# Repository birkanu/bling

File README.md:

# Bling

Bling is a smart ring that lets you control any bluetooth enabled device using hand gestures.

This repository contains:
* [bling-js](https://github.com/birkanu/bling/tree/master/bling-js) (Bling JavaScript Bindings)
* [bling-connection-js](https://github.com/birkanu/bling/tree/master/bling-connection-js) (Bling Connection: JavaScript Component)
* [bling-connection-arduino](https://github.com/birkanu/bling/tree/master/bling-connection-arduino) (Bling Connection: Arduino Component)

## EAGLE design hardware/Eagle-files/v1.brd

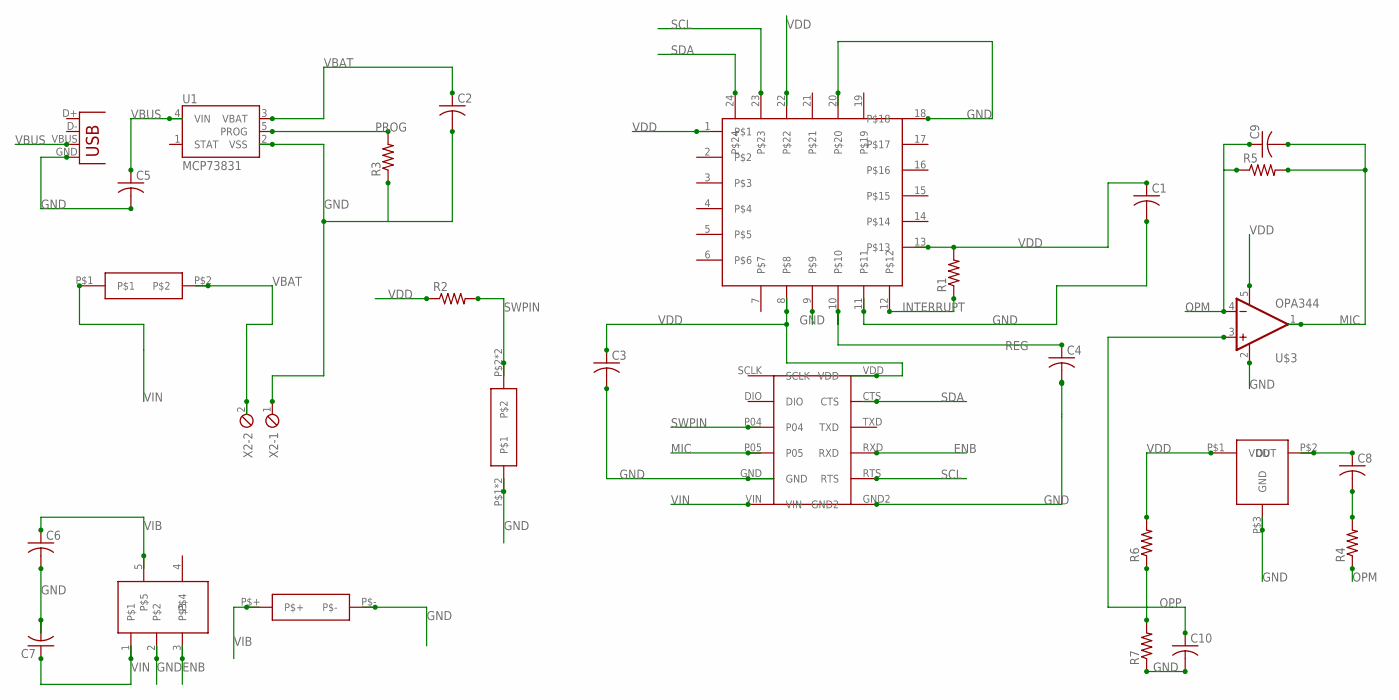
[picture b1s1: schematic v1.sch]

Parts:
C1, C2, C3, C4, C5, C6, C7, C8, C9, C10: C-USC0402K; C0402K
R1, R2, R3, R4, R5, R6, R7: R-US_R0402; R0402
U1: MCP73831; SOT23-5
U$1: NANOBLE
U$2: MICROPHONE
U$3: OPA344; SOT23-5
U$4: LP5907; SOT23-5
U$5: TACTILE
U$6: SWITCH; SWITCH2
U$7: VIBRATOR
U$8: COMPASSE; QFN-24-USB
X1: USB-MICROB
X2: MPT2; 2POL254

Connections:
ENB: U$1.RXD, U$4.3
GND: C1.2, C2.2, C3.2, C4.2, C5.2, C6.2, C7.2, C10.2, R3.1, R7.1, U1.2 (VSS), U$1.GND, U$1.GND2, U$2.P$3 (GND), U$3.2 (V-), U$4.2, U$5.P$1, U$5.P$3, U$7.P$-, U$8.9, U$8.11, U$8.18, U$8.20, X1.GND, X2.1
INTERRUPT: R1.1, U$8.12
MIC: C9.2, R5.2, U$1.P05, U$3.1 (OUT)
unnamed: C8.2, R4.2
unnamed: C8.1, U$2.P$2 (OUT)
OPM: C9.1, R4.1, R5.1, U$3.4 (-IN)
OPP: C10.1, R6.1, R7.2, U$3.3 (+IN)
PROG: R3.2, U1.5 (PROG)
REG: C4.1, U$8.10
SCL: U$1.RTS, U$8.23
SDA: U$1.CTS, U$8.24
SWPIN: R2.2, U$1.P04, U$5.P$2, U$5.P$4
VBAT: C2.1, U1.3 (VBAT), U$6.P$2, X2.2
VBUS: C5.1, U1.4 (VIN), X1.VBUS
VDD: C1.1, C3.1, R1.2, R2.1, R6.2, U$1.VDD, U$2.P$1 (VDD), U$3.5 (V+), U$8.1, U$8.8, U$8.13, U$8.22
VIB: C6.1, U$4.5, U$7.P$+
VIN: C7.1, U$1.VIN, U$4.1, U$6.P$1

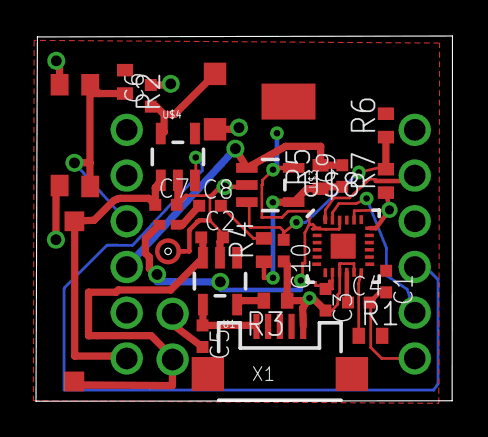
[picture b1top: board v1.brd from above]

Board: 2 copper layers, 23.1 x 20.3 mm, 28 parts (0 on the bottom side), 18 nets.

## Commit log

2015-02-20 Add peripheral connection logic.
2015-02-22 Implement communication between central and peripheral
2015-02-23 Add socket.io communication between server and client
2015-02-23 Add 2048 Example
2015-06-06 Commented out socket.io code
2015-06-06 Commented out data conversion
2015-06-08 Creare README.md
2015-06-08 Restructure file and folders for bling
2015-06-08 Edit README file
2015-06-09 Add hyperlinks to folders inside the repo
2015-06-09 Remove Rhyno variable names
2015-06-09 Edited the app.js file for printing raw acc,gyro and temp values
2015-06-09 Added the BLENano firmware for acquiring data from MPU-6050 and transmitting it with BLE
2015-06-10 Rename Folders and change README files
2015-06-10 Change bling-arduino README file
2015-06-10 Add Bling JavaScript Bindings
2015-06-11 Implement connecting to multiple peripherals
2015-06-14 Add Bling Corporation Documents to the repo
2015-06-15 Remove Bling Business Documents
2015-06-15 Change IMU data reading protocol
2015-06-19 Add and install dependencies for bling-js, and ignore them.
2015-06-19 Modify package.json
2015-06-20 Added new files related to hardware
2015-06-20 New hardware files are added
2015-07-10 Add new JS API (not complete)
2015-07-19 Partially complete JS Framework and the connection-js
2015-07-22 Fixed minor bugs with the framework.
2015-07-22 Fix minor bugs
2015-08-01 Started implementing the Yaw-Pitch-Roll calculations on the Arduino side
2015-08-02 More on the microcontroller side implementation of yaw, pitch and roll calculations
2015-08-02 Implememted the yaw pitch roll, but still needs more updates
2015-08-07 Completed the Yaw-Pitch_Roll calculations on the Arduino side, yaw is not so accurate though
2015-08-08 Add BLE Communication for sending commands to Bling
2015-08-08 Fix typo in app.js of bling-connection-js
2015-08-08 Fix another typo in app.js of bling-connection-js
2015-08-08 Modify test.js to make Bling vibrate when connected
2015-08-10 Implemented the Arduino side of vibrate commands, there are some issues though
2015-08-10 Fix socket's emitting commands
2015-08-10 Moved bling-gesture-detection and hardware folders to Google Drive
2015-08-18 Fix an issue where the COMMAND CHAR wasn't discovered
2015-08-18 Only start scanning for peripherals when Bluetooth is powered on.
2015-08-23 Minor fix

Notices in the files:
parts and their libraries:
ahmed: Licensing: CC v3.0 Share-Alike You are welcome to use this library for commercial purposes.
